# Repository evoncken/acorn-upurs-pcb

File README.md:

# acorn-upurs-pcb

This project contains the KiCad schematic and PCB design for the
[UPURS](https://www.retro-kit.co.uk/UPURS/) Adapter.

UPURS (by Martin Barr) is perfect for transfering Acorn BBC Micro
floppy discs to a PC. All you need is an adapter cable with 2
resistors and 2 diodes.

Designing a PCB for this simple adapter is absolute overkill, but
it allowed me to gain experience with KiCad Schematic entry and PCB
design.

The adapter board has a 20-pin IDC connector for the BBC Micro user
port, and a 9-pin serial port connector for a USB-to-serial adapter
cable.

The printed circuit board was ordered from JLCPCB (not affiliated).
I use a "UGreen USB to RS-232 DB9 Serial Adapter Cable", based on
the Prolific PL2303 chipset.

Credits:
- Martin Barr for creating UPURS
- Paul Vernon of https://retro-kit.co.uk for hosting UPURS
- The wonderful community at https://stardot.org.uk

## Repository layout

- kicad/ contains the KiCad schematic and PCB design files
- kicad/gerbers/ contains the Gerber files as sent to manufacturing
- docs/ contains screenshots and images

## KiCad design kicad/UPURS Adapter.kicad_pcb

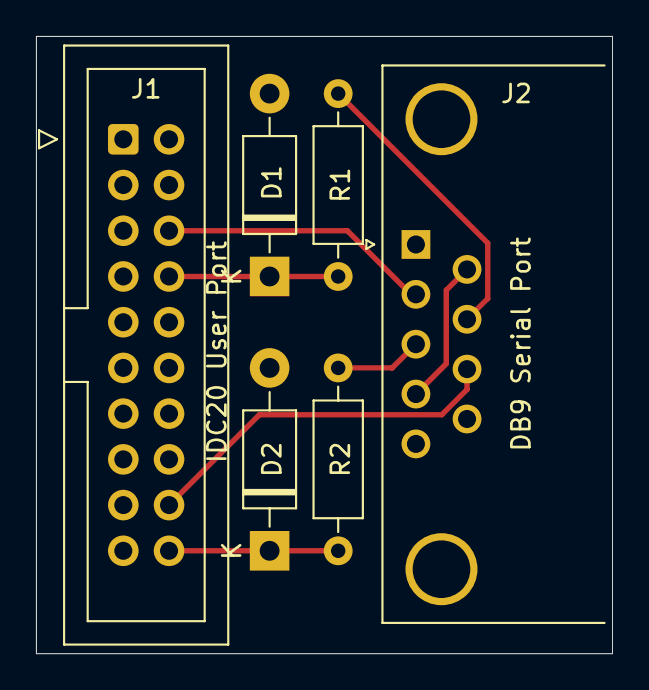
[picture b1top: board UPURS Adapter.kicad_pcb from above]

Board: 2 copper layers, 32.0 x 34.3 mm, 6 parts (0 on the bottom side), 8 nets.

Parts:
D1, D2: 1N4148; D_DO-41_SOD81_P10.16mm_Horizontal
J1: IDC20 User Port; IDC-Header_2x10_P2.54mm_Vertical
J2: DB9 Serial Port; DSUB-9_Female_Horizontal_P2.77x2.84mm_EdgePinOffset7.70mm_H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
R1, R2: 4k7; R_Axial_DIN0207_L6.3mm_D2.5mm_P10.16mm_Horizontal

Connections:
/CTS: J1.18, J2.8
/RTS: D1.1, J1.8, R1.2
/RTS-PC: J2.7, R1.1
/RxD: J1.6, J2.2
/TxD: D2.1, J1.20, R2.2
/TxD-PC: J2.3, R2.1
GND: D1.2, D2.2, J1.5, J1.7, J1.9, J1.11, J1.13, J1.15, J1.17, J1.19, J2.5
unnamed: J2.4, J2.6

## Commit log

2020-10-31 Add KiCad files, screenshots and pictures of the finished PCB
2020-10-31 Add images to README.md
2020-10-31 Credit where credit is due...
